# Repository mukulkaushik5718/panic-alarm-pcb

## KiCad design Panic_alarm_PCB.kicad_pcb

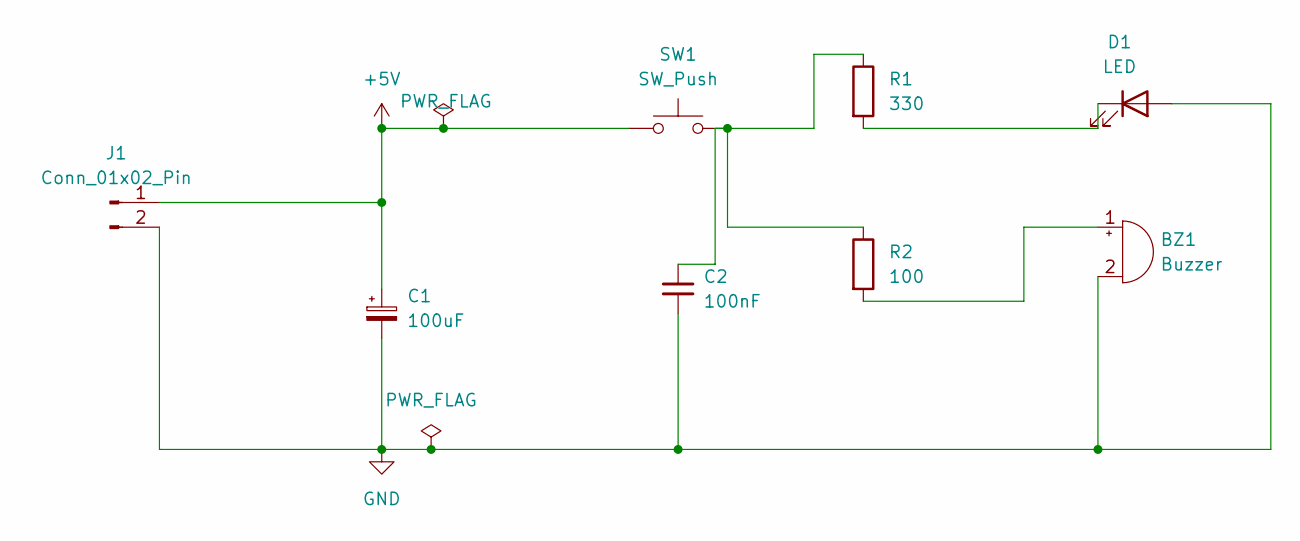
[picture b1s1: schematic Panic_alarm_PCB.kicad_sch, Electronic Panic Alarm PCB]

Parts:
BZ1: Buzzer; Buzzer_12x9.5RM7.6
C1: 100uF; CP_Radial_D5.0mm_P2.00mm
C2: 100nF; C_Disc_D5.0mm_W2.5mm_P5.00mm
D1: LED; LED_D5.0mm
J1: Conn_01x02_Pin; PinHeader_1x02_P2.54mm_Vertical
R1: 330; R_Axial_DIN0207_L6.3mm_D2.5mm_P10.16mm_Horizontal
R2: 100; R_Axial_DIN0207_L6.3mm_D2.5mm_P10.16mm_Horizontal
SW1: SW_Push; SW_PUSH_6mm

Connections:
+5V: C1.1, J1.1, SW1.1
GND: BZ1.2 (-), C1.2, C2.2, D1.2 (A), J1.2
unnamed: BZ1.1 (+), R2.2
unnamed: C2.1, R1.1, R2.1, SW1.2
unnamed: D1.1 (K), R1.2

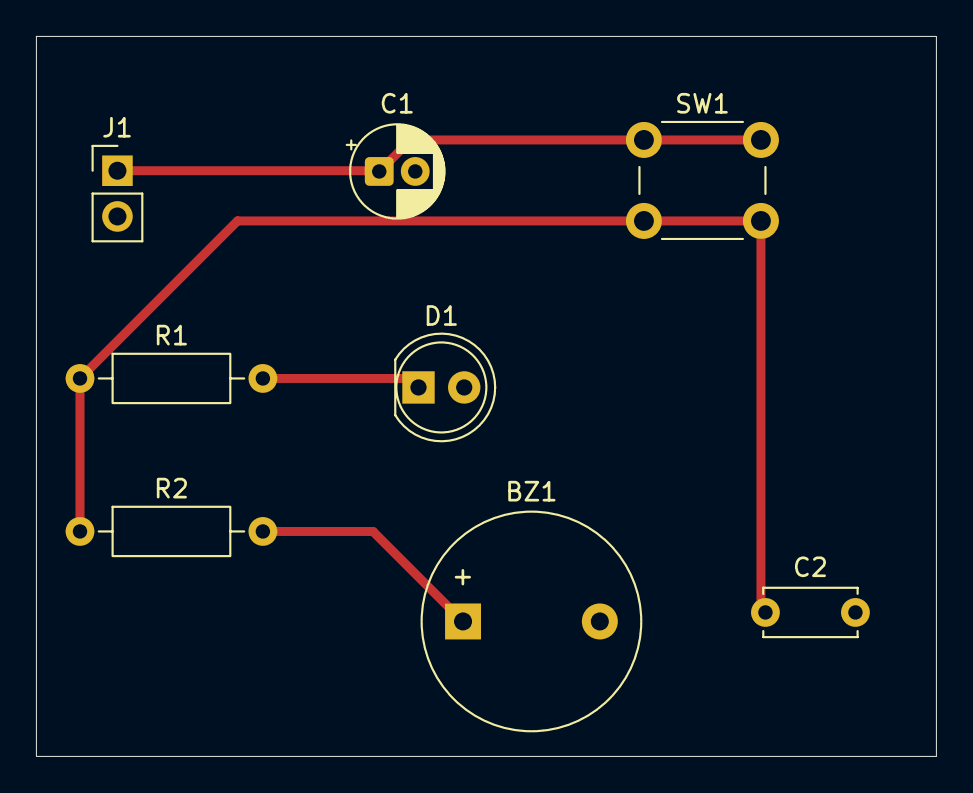
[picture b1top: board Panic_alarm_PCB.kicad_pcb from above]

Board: 2 copper layers, 50.0 x 40.0 mm, 8 parts (0 on the bottom side), 5 nets.
